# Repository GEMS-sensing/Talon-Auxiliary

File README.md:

<!--  -->

# Talon-Auxiliary
Talon daughterboard for [Flight data logger](https://github.com/GEMS-sensing/DFM_-_Flight?tab=readme-ov-file). Designed to interface with [Kestrel](https://github.com/GEMS-sensing/Project-Kestrel) main board. This board is designed to provide data logger with support to interface with analog and pulsed digital signals.
# Repo Roadmap
#### [Documents](Documents/) 

General document and image storage for repo and README

#### [Hardware](Hardware/)

Current board files (Eagle), Bill of Materials (BoM), and other design documents

#### [Production](Production/)

Contains the various Gerber and pick and place files required to have the Printed Circuit Boards (PCBs) manufactured or populated 

#### [Software](Software/)

The software associated with the piece of hardware, this is usually diagnostic software used for verifying or investigating the hardware

<!-- #### [Mechanical](Mechanical/)

Mechanical design files and assembly documents -->

<!-- #### [Testing](Testing/)

Scripts and results from the testing process and development process. Contains more detailed information about documented issues among other testing. 
 -->

## Overview
* **Type:** Talon
* **Interfaces:** Analog, digital, digital (open drain)
* **Release Version:** v1.5 - 2023/05/15

<!--  -->

## Features
### On-Board
* High precision ADC interface
	* 5V input
	* PGA
	* 16 bit (93.75 &mu;V @ 5V input, 3.9 &mu;V @ 0.25V input)
	* up to 860 SPS (reduced resolution)
* Hardware pulse counter
	* Reduces power consumption of logger by eliminating need to wake up SoM for frequent pulse interrupts 
	* 16 bit (65536) pulse count limit
	* Analog front end with hysteresis to deal with noisy inputs
	* Support for self diagnostics to allow for automated testing of operation 
* Push-pull and Open-drain compatible inputs 
* Load switch control for each port with current limiting 
* Manual switches to select each port between 3v3 and 5v power/logic
	* Chosen to be manual to prevent a firmware bug from damaging a sensor
* EEPROM with UUID built in - can store additional values defined by firmware to track offsets, etc
* ESD protected inputs

### Interface - Sensor
* I<sup>2</sup>C data interface
* M12 circular connector 

<!-- <picture>
  <source media="(prefers-color-scheme: dark)" srcset="Documents/Images/Pinout_LIGHT.png">
  
</picture> -->

| **Pin** | **Connection** | **Description** |
|---------|----------------| --------------- |
| 1     | Power (3.3V  **OR** 5V) | Output power to sensors, limited to 50mA continuous current, voltage level is selected by DIP switch next to each port |
| 2     | Open Drain            | Input for switch based sensors - 10k&Omega; pullup to Power rail|
| 3     | Ground            | Power and data ground for system |
| 4      | Analog            | Analog voltage input |
| 5      | Digital | Digital pulse input |

#### Sensor Wiring

- Switch based sensors
	- e.g. reed switch, hall effect, etc
	- Devices where the sensor open or closes a switch depending on state
	- Wire switch between Ground and Open Drain lines
	- WARNING: The Talon will apply rail power to the switch line via a pullup resistor - ensure the sensor is rated for the rail voltage being used (3.3V or 5V)
	- NOTE: To limit power consumption, only recommended for Nominally Open (NO) switches
- Pulse based sensors
	- e.g. microcontroller pulse outputs, basic digital sensors, etc
	- Devices where the output is either 0V or a logic voltage based based on a sensor state
	- Wire grounds together and wire the pulse output to the Digital pin, wire Power to sensor if needed
	- NOTE: The digital input is 5V tolerant regardless of the voltage on the power bus
- Analog based sensors
	- e.g. Potentiometers, basic sensors with variable voltage output, etc
	- Devices where the output is a voltage which varies with sensed value
	- Wire grounds together and wire the analog output of the sensor to the Analog pin, wire Power to sensor if needed
	- NOTE: The analog input is rated up to 5V regardless of the voltage on the power bus

#### Bus Selection
The power provided by each Aux Talon port can be selected as either 3.3V (default) or 5V - depending on the demands of the sensor.

This setting is changed by flipping the DIP switches (`S1`, `S2`, `S3`) on the Aux Talon itself, the position for a given voltage is noted next to each switch. Each switch controls the Aux Talon port it is adjacent to and each port can be switched independently of the others.

> [!WARNING]
> Application of voltage beyond the sensor specifications may result in irreparable damage to the sensor!

<!-- ### Interface
* I<sup>2</sup>C
* M12 circular connector  -->

<!-- <picture>
  <source media="(prefers-color-scheme: dark)" srcset="Documents/Pinout_LIGHT.png">
  
</picture> -->

<!-- ## Specifications
* **Voltage - Supply:** 3.3V
* **Voltage - Logic:** 3.3V
* **Input Current (Avg, 1s period): 30.95&mu;A @ 3.3V**
* **Input Current (Avg, 5s period): 107.43&mu;A @ 3.3V**
* **Input Current (Max): 0.45mA @ 3.3V**

#### Sensor
**Temperature** [^1]
* Range: -40 ~ 125°C 
* Accuracy: &plusmn; 0.2°C
* Repeatability: &plusmn; 0.04°C

**Pressure** [^2]
* Range: 300 ~ 1200 hPa  
* Accuracy: &plusmn; 1 hPa
* Repeatability: &plusmn; 0.06 hPa

**Humidity** [^1]
* Range: 0 ~ 100%
* Accuracy: &plusmn; 2%
* Repeatability: 0.08%

[^1]: [SHT31 Datasheet](https://sensirion.com/media/documents/213E6A3B/63A5A569/Datasheet_SHT3x_DIS.pdf)
[^2]: [DPS368 Datasheet](https://www.infineon.com/dgdl/Infineon-DPS368-DS-v01_00-EN.pdf?fileId=5546d46269e1c019016a0c45105d4b40) -->

<!-- ## Version History

`v0.0` - Initial primal version with screw terminal

`v0.1` - Initial 'hard mount' version, using M12 connector

`v1.0` - Removed pullup select[^3], added logic level buffer and voltage reg on input

`v1.1` - Moved via away from connector pads to prevent bridging when soldering 

`v2.0` - Fixed issue with address select jumper[^3] -->

<!-- ## Jumper Settings 

> [!IMPORTANT]
> Jumper settings valid for version `v2.0` and beyond[^3]

[^3]: See Errata

**Configuration Jumpers**
| Jumper | Purpose | Open | Closed | Default | 
| ------ | ------- | ---------- | ---------- | ----- | 
| `JP1` | I<sup>2</sup>C Address Select | Base Address<sup>&dagger;</sup> | Alt Address<sup>&Dagger;</sup> | Open |

&dagger; SHT31 = `0x44`, DPS368 = `0x76`

&Dagger; SHT31 = `0x44`, DPS368 = `0x77`
 -->

## Known Issues/Errata

None
<!-- #### Solder Jumper Stencil

**Version Affected:** All

**Issue:** Solar input does not support very low impedance sources (e.g. lead acid battery) - see details in issue [#20](https://github.com/GEMS-sensing/Project-Kestrel/issues/20)

**Workaround:** 

* Avoid use of low impedance batteries for input
* Include series impedance to prevent current spikes (not desirable)
* Perform board patch described in issue [#20](https://github.com/GEMS-sensing/Project-Kestrel/issues/20) -->

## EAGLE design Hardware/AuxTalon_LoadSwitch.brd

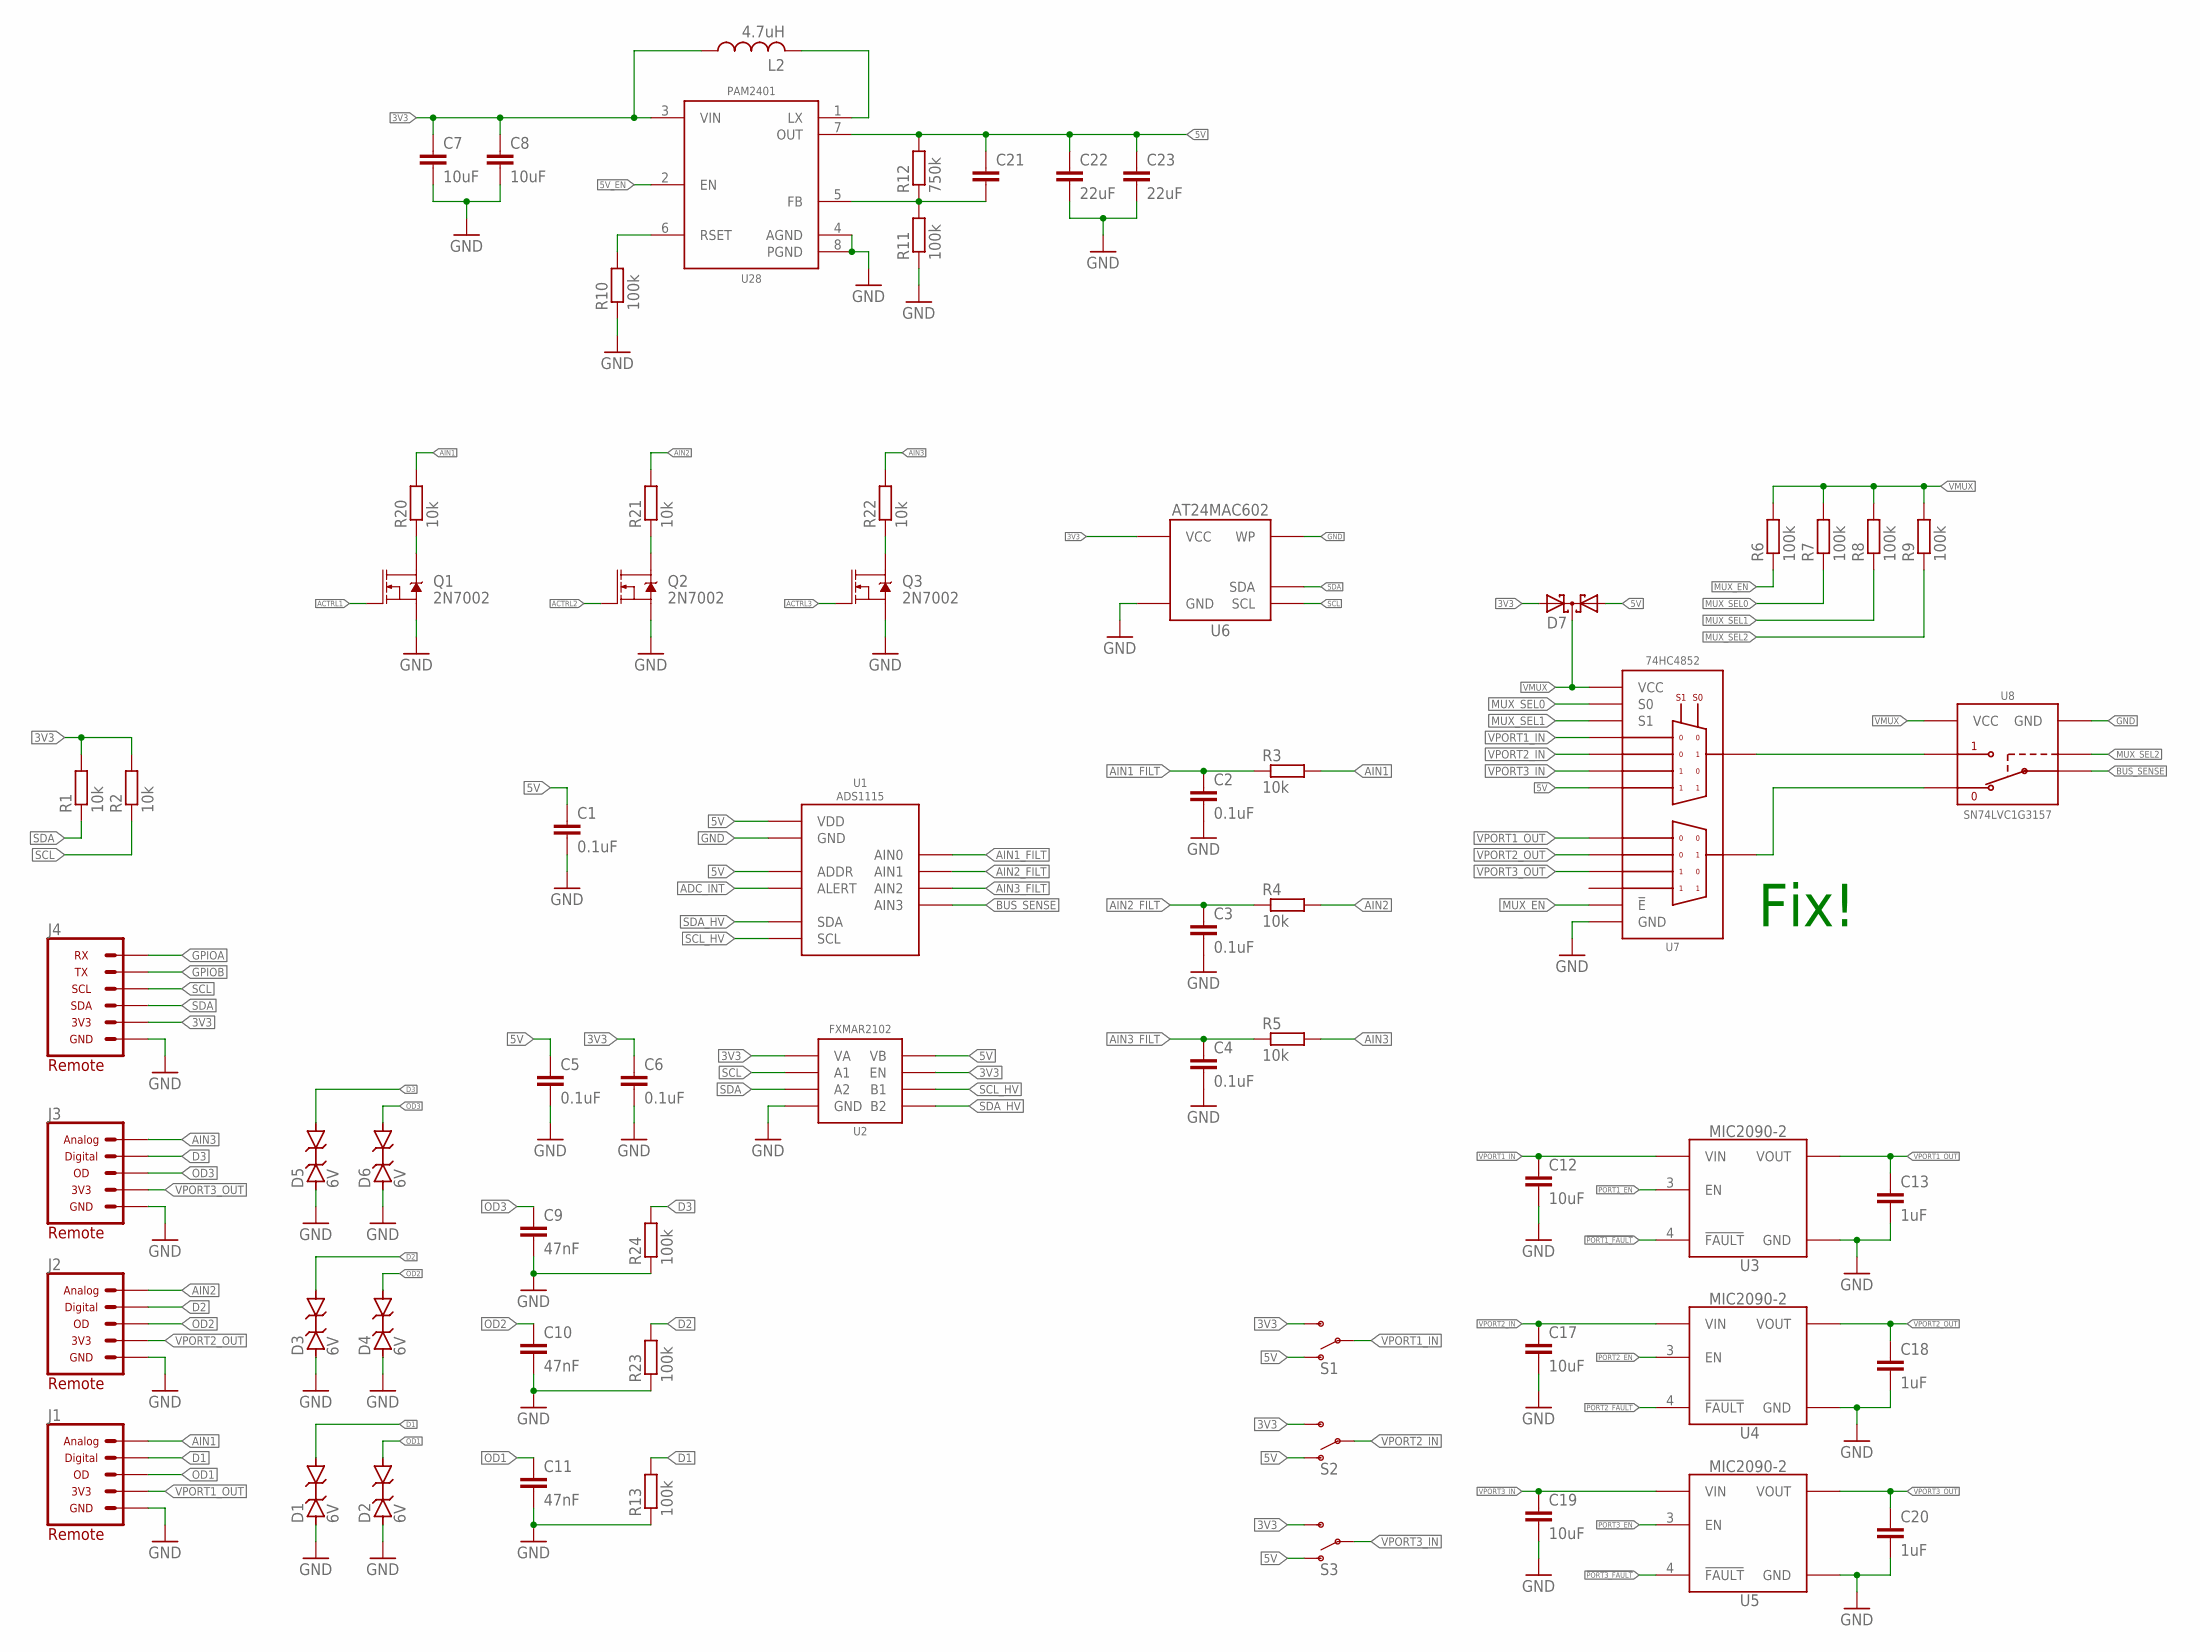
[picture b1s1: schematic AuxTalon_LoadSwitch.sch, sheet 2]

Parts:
C1, C5, C6: 0.1uF; C0402
C2, C3, C4: 0.1uF; C0805
C7, C8, C12, C17, C19: 10uF; C0805
C9, C10, C11: 47nF; C0402
C13, C18, C20: 1uF; C0603
C21: C-EUC0402; C0402; MPN DNP; DIGIKEY DNP
C22, C23: 22uF; C0805
D1, D2, D3, D4, D5, D6: 6V; D0402
D7: DIODE_CCBAT54CSOT23; SOT23-3
J1, J2, J3: CONN_AUX_M12_REMOTE; 1X05_M12_TE_T41410
J4: CONN_TALON_REMOTE; 1X06_MICROLOCKPLUS
L2: 4.7uH; WE-MAPI(2.5X2); MPN 74438323047; DIGIKEY 732-4848-1-ND
Q1, Q2, Q3: 2N7002; SOT23-3
R1, R2, R3, R4, R5, R20, R21, R22: 10k; R0402
R6, R7, R8, R9, R13, R23, R24: 100k; R0402
R10, R11: 100k; R0603
R12: 750k; R0603
S1, S2, S3: SPDTCAS-120A1; CAS-120A1
U1: ADS1115; VSSOP_10
U2: FXMAR2102UMLP; UQFN-8_1.4X1.2
U3, U4, U5: MIC2090-2; SOT23-5
U6: AT24MAC602SOT23; SOT23-5
U7: 74HC4852; VQFN-16
U8: SN74LVC1G3157SC70; DCK_R-PDSO-G6
U28: PAM2401MSOP; MSOP_8

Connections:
3V3: C6.1, C7.1, C8.1, D7.2 (A2), J4.2 (3V3), L2.P$1 (1), R1.2, R2.2, S1.3 (S), S2.3 (S), S3.3 (S), U2.1 (VA), U2.5 (EN), U6.4 (VCC), U28.3 (VIN); also elsewhere on the board
5V: C1.1, C5.1, C21.1, C22.1, C23.1, D7.1 (A1), R12.2, S1.1 (O), S2.1 (O), S3.1 (O), U1.1 (ADDR), U1.8 (VDD), U2.8 (VB), U7.11 (1Y3), U28.7 (OUT)
5V_EN: U28.2 (EN); also elsewhere on the board
!PORT1_FAULT: U3.4 (!FAULT); also elsewhere on the board
!PORT2_FAULT: U4.4 (!FAULT); also elsewhere on the board
!PORT3_FAULT: U5.4 (!FAULT); also elsewhere on the board
ACTRL1: Q1.1 (G); also elsewhere on the board
ACTRL2: Q2.1 (G); also elsewhere on the board
ACTRL3: Q3.1 (G); also elsewhere on the board
ADC_INT: U1.2 (ALERT); also elsewhere on the board
AIN1: J1.4 (ANALOG), R3.2, R20.2
AIN1_FILT: C2.1, R3.1, U1.4 (AIN0)
AIN2: J2.4 (ANALOG), R4.2, R21.2
AIN2_FILT: C3.1, R4.1, U1.5 (AIN1)
AIN3: J3.4 (ANALOG), R5.2, R22.2
AIN3_FILT: C4.1, R5.1, U1.6 (AIN2)
BUS_SENSE: U1.7 (AIN3), U8.4 (A)
D1: D1.2 (C), J1.5 (DIGITAL), R13.2; also elsewhere on the board
D2: D3.2 (C), J2.5 (DIGITAL), R23.2; also elsewhere on the board
D3: D5.2 (C), J3.5 (DIGITAL), R24.2; also elsewhere on the board
GND: C1.2, C2.2, C3.2, C4.2, C5.2, C6.2, C7.2, C8.2, C9.2, C10.2, C11.2, C12.2, C13.2, C17.2, C18.2, C19.2, C20.2, C22.2, C23.2, D1.1 (A), D2.1 (A), D3.1 (A), D4.1 (A), D5.1 (A), D6.1 (A), J1.3 (GND), J2.3 (GND), J3.3 (GND), J4.1 (GND), Q1.2 (S), Q2.2 (S), Q3.2 (S), R10.1, R11.1, R13.1, R23.1, R24.1, U1.3 (GND), U2.4 (GND), U3.2 (GND), U4.2 (GND), U5.2 (GND), U6.2 (GND), U6.5 (WP), U7.8 (GND), U7.EP (GND), U8.2 (GND), U28.4 (AGND), U28.8 (PGND); also elsewhere on the board
GPIOA: J4.6 (RX); also elsewhere on the board
GPIOB: J4.5 (TX); also elsewhere on the board
MUX_EN: R6.1, U7.6 (!E); also elsewhere on the board
MUX_SEL0: R7.1, U7.10 (S0); also elsewhere on the board
MUX_SEL1: R8.1, U7.9 (S1); also elsewhere on the board
MUX_SEL2: R9.1, U8.6 (S); also elsewhere on the board
unnamed: U7.3 (2Z), U8.3 (B1)
unnamed: R10.2, U28.6 (RSET)
unnamed: C21.2, R11.2, R12.1, U28.5 (FB)
unnamed: Q3.3 (D), R22.1
unnamed: Q2.3 (D), R21.1
unnamed: Q1.3 (D), R20.1
unnamed: L2.P$2 (2), U28.1 (LX)
unnamed: U7.13 (1Z), U8.1 (B2)
OD1: C11.1, D2.2 (C), J1.2 (DIGITAL_OPENDRAIN); also elsewhere on the board
OD2: C10.1, D4.2 (C), J2.2 (DIGITAL_OPENDRAIN); also elsewhere on the board
OD3: C9.1, D6.2 (C), J3.2 (DIGITAL_OPENDRAIN); also elsewhere on the board
PORT1_EN: U3.3 (EN); also elsewhere on the board
PORT2_EN: U4.3 (EN); also elsewhere on the board
PORT3_EN: U5.3 (EN); also elsewhere on the board
SCL: J4.4 (SCL), R2.1, U2.2 (A1), U6.1 (SCL); also elsewhere on the board
SCL_HV: U1.10 (SCL), U2.7 (B1)
SDA: J4.3 (SDA), R1.1, U2.3 (A2), U6.3 (SDA); also elsewhere on the board
SDA_HV: U1.9 (SDA), U2.6 (B2)
VMUX: D7.3 (C), R6.2, R7.2, R8.2, R9.2, U7.16 (VCC), U8.5 (VCC)
VPORT1_IN: C12.1, S1.2, U3.1 (VIN), U7.12 (1Y0)
VPORT1_OUT: C13.1, J1.1 (3V3), U3.5 (VOUT), U7.1 (2Y0)
VPORT2_IN: C17.1, S2.2, U4.1 (VIN), U7.14 (1Y1)
VPORT2_OUT: C18.1, J2.1 (3V3), U4.5 (VOUT), U7.5 (2Y1)
VPORT3_IN: C19.1, S3.2, U5.1 (VIN), U7.15 (1Y2)
VPORT3_OUT: C20.1, J3.1 (3V3), U5.5 (VOUT), U7.2 (2Y2)

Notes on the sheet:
Fix!

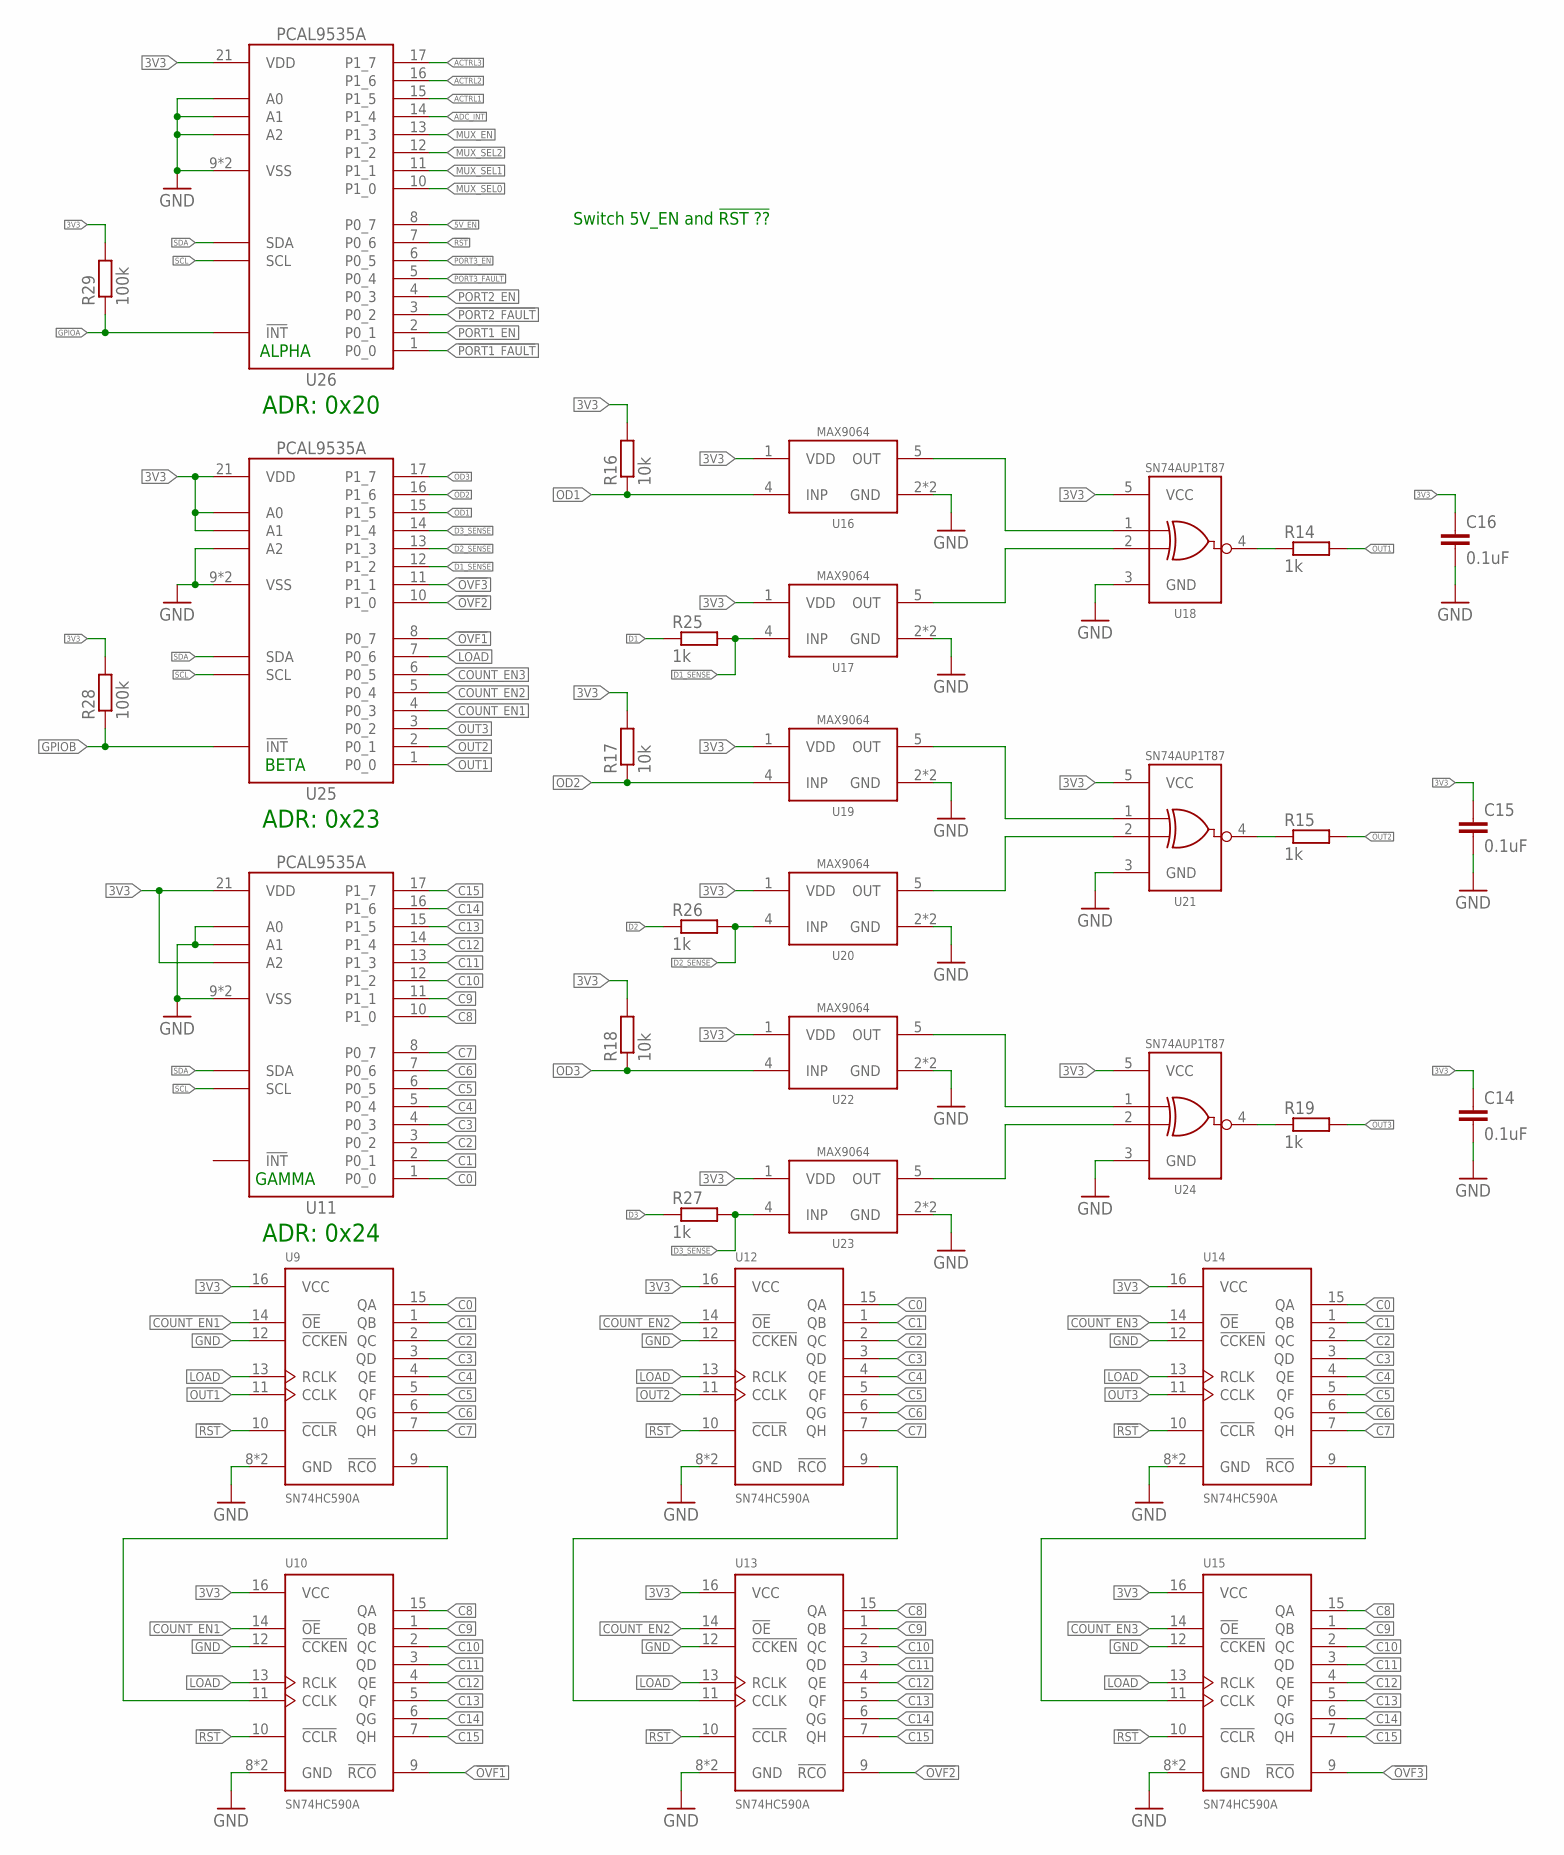
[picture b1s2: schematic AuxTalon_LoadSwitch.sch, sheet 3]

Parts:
C14, C15, C16: 0.1uF; C0402
R14, R15, R19, R25, R26, R27: 1k; R0402
R16, R17, R18: 10k; R0402
R28, R29: 100k; R0402
U9, U10, U12, U13, U14, U15: SN74HC590AVQFN; VQFN-16
U11, U25, U26: PCAL9535AQFN; QFN24
U16, U17, U19, U20, U22, U23: MAX9064; SOT23-5
U18, U21, U24: SN74AUP1T87; DCK_R-PDSO-G5

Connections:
3V3: C14.1, C15.1, C16.1, R16.2, R17.2, R18.2, R28.2, R29.2, U9.16 (VCC), U10.16 (VCC), U11.21 (VDD), U11.24 (A2), U12.16 (VCC), U13.16 (VCC), U14.16 (VCC), U15.16 (VCC), U16.1 (VDD), U17.1 (VDD), U18.5 (VCC), U19.1 (VDD), U20.1 (VDD), U21.5 (VCC), U22.1 (VDD), U23.1 (VDD), U24.5 (VCC), U25.18 (A0), U25.21 (VDD), U25.23 (A1), U26.21 (VDD); also elsewhere on the board
5V_EN: U26.8 (P0_7); also elsewhere on the board
!OVF1: U10.9 (!RCO), U25.8 (P0_7)
!OVF2: U13.9 (!RCO), U25.10 (P1_0)
!OVF3: U15.9 (!RCO), U25.11 (P1_1)
!PORT1_FAULT: U26.1 (P0_0); also elsewhere on the board
!PORT2_FAULT: U26.3 (P0_2); also elsewhere on the board
!PORT3_FAULT: U26.5 (P0_4); also elsewhere on the board
!RST: U9.10 (!CCLR), U10.10 (!CCLR), U12.10 (!CCLR), U13.10 (!CCLR), U14.10 (!CCLR), U15.10 (!CCLR), U26.7 (P0_6)
ACTRL1: U26.15 (P1_5); also elsewhere on the board
ACTRL2: U26.16 (P1_6); also elsewhere on the board
ACTRL3: U26.17 (P1_7); also elsewhere on the board
ADC_INT: U26.14 (P1_4); also elsewhere on the board
C0: U9.15 (QA), U11.1 (P0_0), U12.15 (QA), U14.15 (QA)
C1: U9.1 (QB), U11.2 (P0_1), U12.1 (QB), U14.1 (QB)
C2: U9.2 (QC), U11.3 (P0_2), U12.2 (QC), U14.2 (QC)
C3: U9.3 (QD), U11.4 (P0_3), U12.3 (QD), U14.3 (QD)
C4: U9.4 (QE), U11.5 (P0_4), U12.4 (QE), U14.4 (QE)
C5: U9.5 (QF), U11.6 (P0_5), U12.5 (QF), U14.5 (QF)
C6: U9.6 (QG), U11.7 (P0_6), U12.6 (QG), U14.6 (QG)
C7: U9.7 (QH), U11.8 (P0_7), U12.7 (QH), U14.7 (QH)
C8: U10.15 (QA), U11.10 (P1_0), U13.15 (QA), U15.15 (QA)
C9: U10.1 (QB), U11.11 (P1_1), U13.1 (QB), U15.1 (QB)
C10: U10.2 (QC), U11.12 (P1_2), U13.2 (QC), U15.2 (QC)
C11: U10.3 (QD), U11.13 (P1_3), U13.3 (QD), U15.3 (QD)
C12: U10.4 (QE), U11.14 (P1_4), U13.4 (QE), U15.4 (QE)
C13: U10.5 (QF), U11.15 (P1_5), U13.5 (QF), U15.5 (QF)
C14: U10.6 (QG), U11.16 (P1_6), U13.6 (QG), U15.6 (QG)
C15: U10.7 (QH), U11.17 (P1_7), U13.7 (QH), U15.7 (QH)
COUNT_EN1: U9.14 (!OE), U10.14 (!OE), U25.4 (P0_3)
COUNT_EN2: U12.14 (!OE), U13.14 (!OE), U25.5 (P0_4)
COUNT_EN3: U14.14 (!OE), U15.14 (!OE), U25.6 (P0_5)
D1: R25.1; also elsewhere on the board
D1_SENSE: R25.2, U17.4 (INP), U25.12 (P1_2)
D2: R26.1; also elsewhere on the board
D2_SENSE: R26.2, U20.4 (INP), U25.13 (P1_3)
D3: R27.1; also elsewhere on the board
D3_SENSE: R27.2, U23.4 (INP), U25.14 (P1_4)
GND: C14.2, C15.2, C16.2, U9.8 (GND), U9.12 (!CCKEN), U9.EP (GND), U10.8 (GND), U10.12 (!CCKEN), U10.EP (GND), U11.9 (VSS), U11.18 (A0), U11.23 (A1), U11.EP (VSS), U12.8 (GND), U12.12 (!CCKEN), U12.EP (GND), U13.8 (GND), U13.12 (!CCKEN), U13.EP (GND), U14.8 (GND), U14.12 (!CCKEN), U14.EP (GND), U15.8 (GND), U15.12 (!CCKEN), U15.EP (GND), U16.2 (GND), U16.3 (GND), U17.2 (GND), U17.3 (GND), U18.3 (GND), U19.2 (GND), U19.3 (GND), U20.2 (GND), U20.3 (GND), U21.3 (GND), U22.2 (GND), U22.3 (GND), U23.2 (GND), U23.3 (GND), U24.3 (GND), U25.9 (VSS), U25.24 (A2), U25.EP (VSS), U26.9 (VSS), U26.18 (A0), U26.23 (A1), U26.24 (A2), U26.EP (VSS); also elsewhere on the board
GPIOA: R29.1, U26.22 (!INT); also elsewhere on the board
GPIOB: R28.1, U25.22 (!INT); also elsewhere on the board
LOAD: U9.13 (RCLK), U10.13 (RCLK), U12.13 (RCLK), U13.13 (RCLK), U14.13 (RCLK), U15.13 (RCLK), U25.7 (P0_6)
MUX_EN: U26.13 (P1_3); also elsewhere on the board
MUX_SEL0: U26.10 (P1_0); also elsewhere on the board
MUX_SEL1: U26.11 (P1_1); also elsewhere on the board
MUX_SEL2: U26.12 (P1_2); also elsewhere on the board
unnamed: U9.9 (!RCO), U10.11 (CCLK)
unnamed: U12.9 (!RCO), U13.11 (CCLK)
unnamed: U14.9 (!RCO), U15.11 (CCLK)
unnamed: U20.5 (OUT), U21.2 (B)
unnamed: U19.5 (OUT), U21.1 (A)
unnamed: U16.5 (OUT), U18.1 (A)
unnamed: U17.5 (OUT), U18.2 (B)
unnamed: U23.5 (OUT), U24.2 (B)
unnamed: U22.5 (OUT), U24.1 (A)
unnamed: R14.1, U18.4 (Y)
unnamed: R15.1, U21.4 (Y)
unnamed: R19.1, U24.4 (Y)
OD1: R16.1, U16.4 (INP), U25.15 (P1_5); also elsewhere on the board
OD2: R17.1, U19.4 (INP), U25.16 (P1_6); also elsewhere on the board
OD3: R18.1, U22.4 (INP), U25.17 (P1_7); also elsewhere on the board
OUT1: R14.2, U9.11 (CCLK), U25.1 (P0_0)
OUT2: R15.2, U12.11 (CCLK), U25.2 (P0_1)
OUT3: R19.2, U14.11 (CCLK), U25.3 (P0_2)
PORT1_EN: U26.2 (P0_1); also elsewhere on the board
PORT2_EN: U26.4 (P0_3); also elsewhere on the board
PORT3_EN: U26.6 (P0_5); also elsewhere on the board
SCL: U11.19 (SCL), U25.19 (SCL), U26.19 (SCL); also elsewhere on the board
SDA: U11.20 (SDA), U25.20 (SDA), U26.20 (SDA); also elsewhere on the board

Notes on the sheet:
BETA
GAMMA
ALPHA
ADR: 0x20
ADR: 0x23
ADR: 0x24
Switch 5V_EN and !RST ??

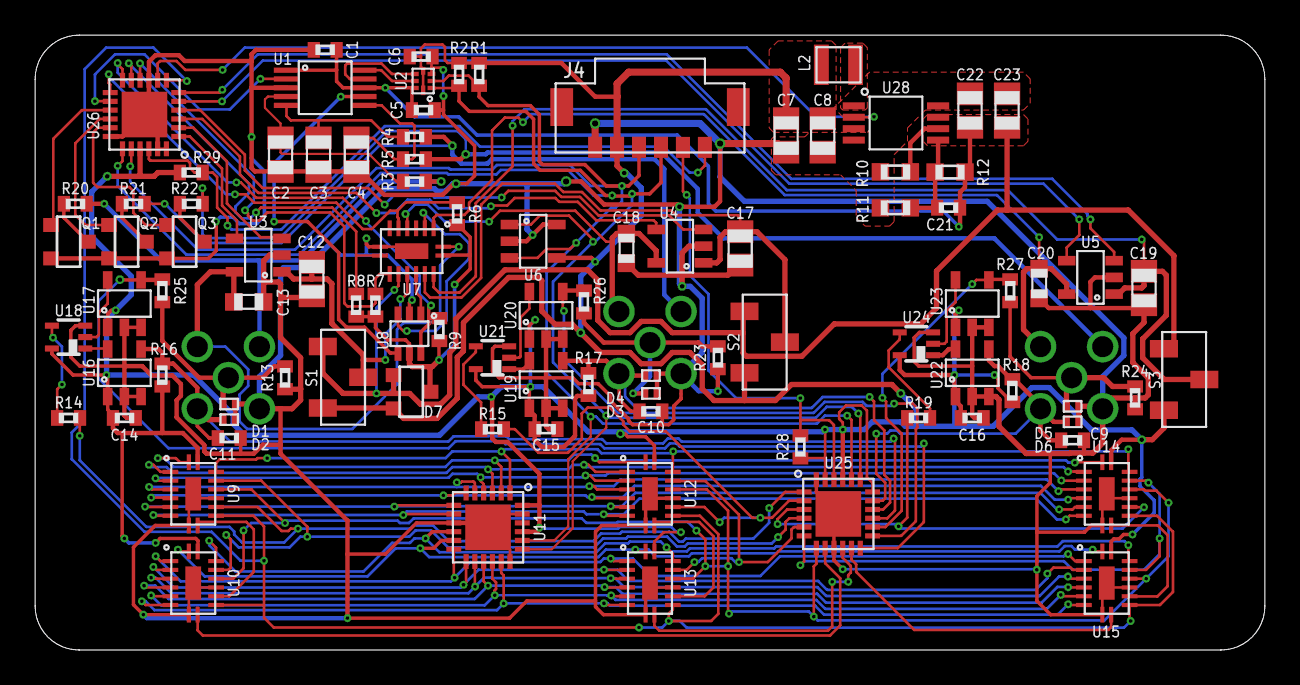
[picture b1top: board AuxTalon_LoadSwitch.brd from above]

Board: 2 copper layers, 70.0 x 35.0 mm, 97 parts (0 on the bottom side), 94 nets.

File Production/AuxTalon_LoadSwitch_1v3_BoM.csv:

"Qty","Value","Device","Package","Parts","Description","DIGIKEY","DISP","MF","MOUSER","MPN","VALUE","VALUE_PART",
"1","","C-EUC0402","C0402","C21","CAPACITOR, European symbol","DNP","","N/A","","DNP","","",
"1","","DIODE_CCBAT54CSOT23","SOT23-3","D7","Dual Diode, Common Cathode","BAT54CLT1GOSCT-ND","","ON Semiconductor","","BAT54CLT1G","","",
"6","","SN74HC590AVQFN","VQFN-16","U9, U10, U12, U13, U14, U15","SN74HC590A - 8 bit binary counter with direct clear","1727-6923-1-ND","","Nexperia","","74HC590BQ","115","",
"9","0.1uF","C-EU0.1UFC0402","C0402","C1, C5, C6, C13, C14, C15, C16, C18, C20","CAPACITOR, European symbol","490-4759-1-ND","","Murata","","GCM155R71C104KA55D","","",
"3","0.1uF","C-EU0.1UFC0805","C0805","C2, C3, C4","CAPACITOR, European symbol","399-8000-1-ND","","Kemet","","C0805C104M3RACTU","","",
"8","100k","R-EU_100KR0402","R0402","R6, R7, R8, R9, R10, R13, R23, R24","RESISTOR, European symbol","311-100KLRCT-ND","","Yageo","","RC0402FR-07100KL","","100k",
"1","100k","R-EU_100KR0603","R0603","R11","RESISTOR, European symbol","311-100KHRCT-ND","","Yageo","","RC0603FR-07100KL","","100k",
"8","10k","R-EU_10KR0402","R0402","R1, R2, R3, R4, R5, R16, R17, R18","RESISTOR, European symbol","311-10.0KLRCT-ND","","Yageo","","RC0402FR-0710KL","","10k",
"1","10k","R-EU_10KR0603","R0603","R21","RESISTOR, European symbol","311-10.0KHRCT-ND","","Yageo","","RC0603FR-0710KL","","10k",
"5","10uF","C-EU10UFC0805","C0805","C7, C8, C12, C17, C19","CAPACITOR, European symbol","490-6473-1-ND","","Murata","","GRM21BR61C106KE15K","","",
"1","150k","R-EU_150KR0603","R0603","R22","RESISTOR, European symbol","311-150KHRCT-ND","","Yageo","","RC0603FR-07150KL","","150k",
"2","22uF","C-EU22UFC0805","C0805","C22, C23","CAPACITOR, European symbol","490-9952-1-ND","","Murata","","GRM219R61C226ME15L","","",
"1","24AA02SOT23","24AA02SOT23","SOT23-5","U6","24AA02 - 2k I2C Serial EEPROM","24AA025E64T-I/OTCT-ND","24AA025E64","Microchip","24AA025E64T-I/OTCT-ND","24AA025E64T-I/OT","","",
"1","4.7uH","INDUCTOR_MAPI_2.5X2","WE-MAPI(2.5X2)","L2","Genaric Inductor","732-4848-1-ND","","Wurth","","74438323047","","",
"3","47nF","C-EU47NFC0402","C0402","C9, C10, C11","CAPACITOR, European symbol","490-3254-1-ND","","Murata","","GRM155R71E473KA88D","","",
"2","62k","R-EU_62KR0603","R0603","R15, R19","RESISTOR, European symbol","RMCF0603FT62K0CT-ND","","Stackpole","","RMCF0603FT62K0","","62k",
"6","6V","DIODE_ESD_BI_D5V0L1_0402","D0402","D1, D2, D3, D4, D5, D6","Generic Bidirectional ESD Diode","D5V0L1B2LP4-7BDICT-ND","","Diodes Inc","","D5V0L1B2LP4-7B","6V","",
"1","74HC4852","74HC4852","VQFN-16","U7","74HC4852  - Analog Multiplexer, Dual 4-Channel (1:4 x 2)","1727-7953-1-ND","74HC4852","Nexperia","","74HC4852BQ-Q100","11","",
"1","750k","R-EU_750KR0603","R0603","R12","RESISTOR, European symbol","311-750KHRCT-ND","","Yageo","","RC0603FR-07750KL","","750k",
"2","82k","R-EU_82KR0603","R0603","R14, R20","RESISTOR, European symbol","CR0603-FX-8202ELFCT-ND","","Bourns","","CR0603-FX-8202ELF","","82k",
"1","ADS1115","ADS1115","VSSOP_10","U1","ADS1115 - Sigma Delta ADC","296-38849-1-ND","","TI","","ADS1115IDGSR","","",
"3","CONN_AUX_M12_REMOTE","CONN_AUX_M12_REMOTE","1X05_M12_TE_T41410","J1, J2, J3","GEMS Connector for Auiliary Port Devices","A126851-ND","Remote","TE","","T4141012051-000","","",
"1","CONN_TALON_REMOTE","CONN_TALON_REMOTE","1X06_MICROLOCKPLUS","J4","GEMS Connector for Talon Interface","900-2059570671CT-ND","Remote","Molex","","2059570671","","",
"1","FXMAR2102UMLP","FXMAR2102UMLP","UQFN-8_1.4X1.2","U2","FXMAR2102 - 2 Channel Bidirectional Voltage Level Translator for I2C Applications","FXMAR2102UMX-F106CT-ND","FXMAR2102","OnSemi","","FXMAR2102UMX-F106","","",
"6","MAX9064","MAX9064","SOT23-5","U16, U17, U19, U20, U22, U23","MAX906x - Ultra-Small nanoPower Single Comparator","MAX9064EUK+TCT-ND","MAX9064","Maxim","","MAX9064EUK+T","","",
"3","MCP23018QFN","MCP23018QFN","QFN24","U11, U25, U26","MCP23018 - I2C I/O Expander, 16 bit wtih interrupt and reset","MCP23018T-E/MJCT-ND","","TI","","MCP23018T-E/MJ","","",
"1","PAM2401MSOP","PAM2401MSOP","MSOP_8","U28","PAM2401 - Step-Up (Boost) DC-DC Converter","PAM2401SCADJDICT-ND","","Diodes Inc","","PAM2401SCADJ","","",
"3","SN74AUP1T87","SN74AUP1T87","DCK_R-PDSO-G5","U18, U21, U24","SN74AUP1T87 - XNOR, 1 Element, 2 Input","296-27398-1-ND","SN74AUP1T87","TI","","SN74AUP1T87DCKR","","",
"1","SN74LVC1G3157SC70","SN74LVC1G3157SC70","DCK_R-PDSO-G6","U8","SN74LVC1G3157 - SPDT Analog Switch","296-14909-1-ND","SN74LVC1G3157","TI","","SN74LVC1G3157DCKR","","",
"3","SPDTCAS-120A1","SPDTCAS-120A1","CAS-120A1","S1, S2, S3","Genaric SPDT switch","CAS120JCT-ND","","Nidec Copal","","CAS-120TA","","",
"3","TPS22944","TPS22944","DCK_R-PDSO-G5","U3, U4, U5","TPS2294x - Low Input Voltage Current Limited Load Switch with Shut off and Auto Restart","2156-FPF2006-ND","FPF2006","Fairchild","","FPF2006","","",

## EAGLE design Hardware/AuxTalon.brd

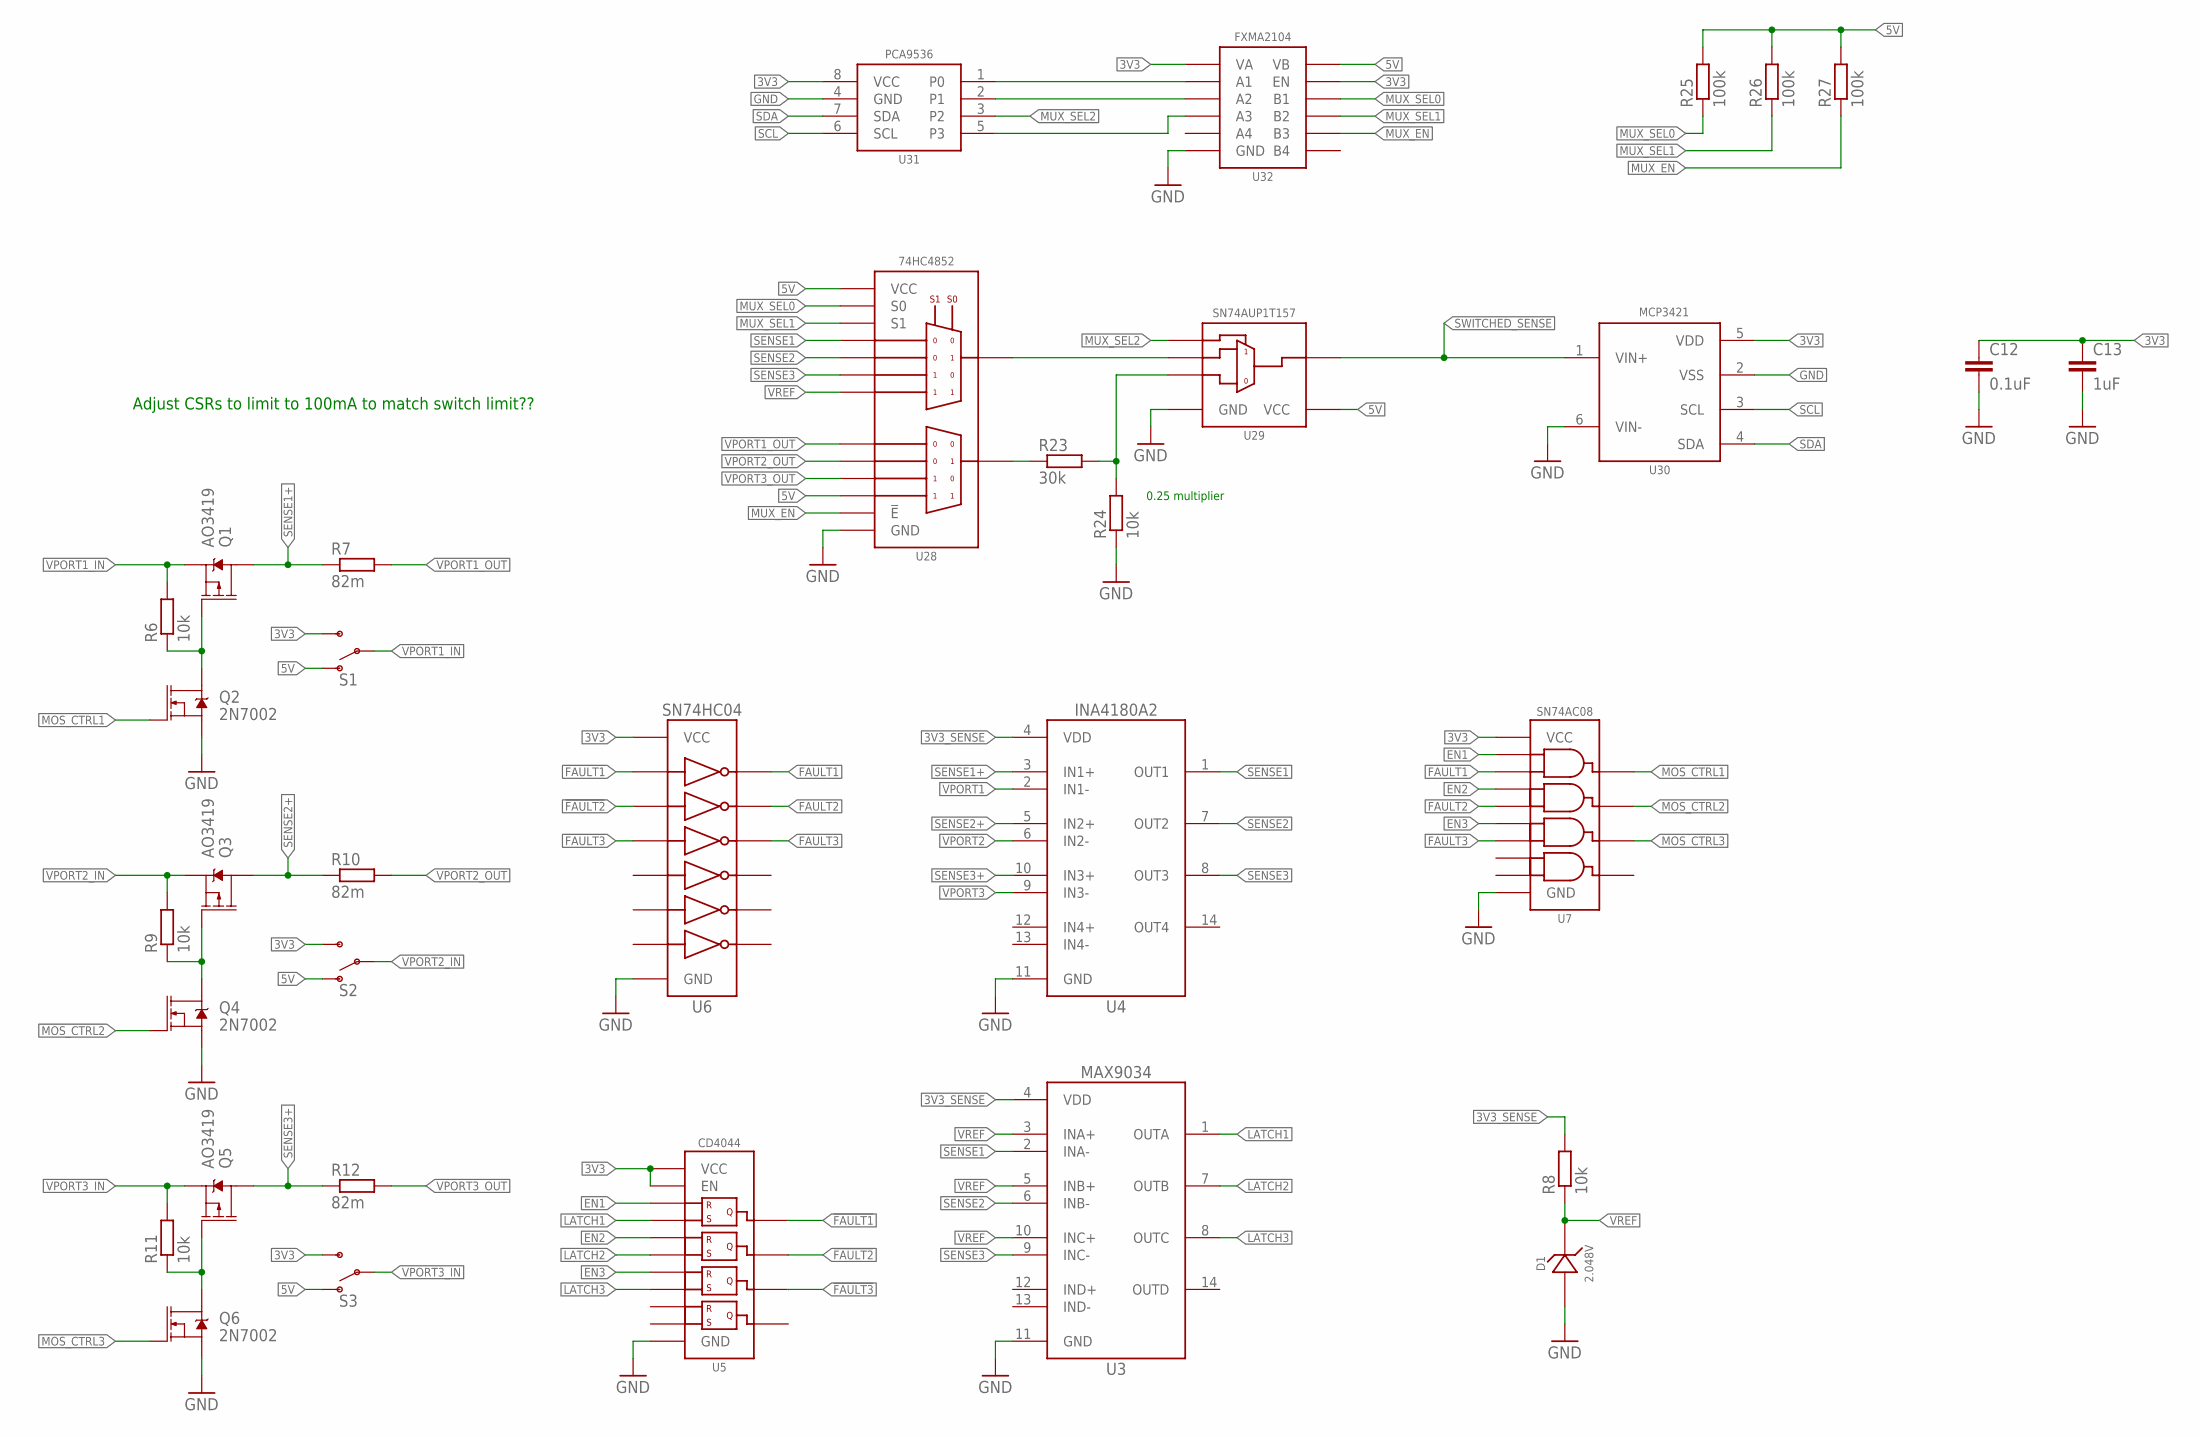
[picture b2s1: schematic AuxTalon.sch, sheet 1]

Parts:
C12: 0.1uF; C0402
C13: 1uF; C0805
D1: 2.048V; SOT23-3
Q1, Q3, Q5: AO3419; SOT23-3
Q2, Q4, Q6: 2N7002; SOT23-3
R6, R8, R9, R11, R24: 10k; R0402
R7, R10, R12: 82m; R0603
R23: 30k; R0402
R25, R26, R27: 100k; R0402
S1, S2, S3: SPDTCAS-120A1; CAS-120A1
U3: MAX9034TSSOP; TSSOP14
U4: INA4180A2; TSSOP14
U5: CD4044; TSSOP16
U6: SN74HC04; TSSOP14
U7: SN74AC08; TSSOP14
U28: 74HC4852; VQFN-16
U29: SN74AUP1T157DCK; DCK_R-PDSO-G6
U30: MCP3421A3; SOT23-6L
U31: PCA9536DFN; DFN_8_3X3
U32: FXMA2104; MLP_12

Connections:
3V3: C12.1, C13.1, S1.3 (S), S2.3 (S), S3.3 (S), U5.5 (EN), U5.16 (VCC), U6.14 (VCC), U7.14 (VCC), U30.5 (VDD), U31.8 (VCC), U32.2 (VA), U32.8 (EN); also elsewhere on the board
3V3_SENSE: R8.2, U3.4 (VDD), U4.4 (VDD); also elsewhere on the board
5V: R25.2, R26.2, R27.2, S1.1 (O), S2.1 (O), S3.1 (O), U28.4 (2Y3), U28.16 (VCC), U29.5 (VCC), U32.1 (VB); also elsewhere on the board
!FAULT1: U5.13 (Q1), U6.1 (A1); also elsewhere on the board
!FAULT2: U5.9 (Q2), U6.3 (A2); also elsewhere on the board
!FAULT3: U5.10 (Q3), U6.5 (A3); also elsewhere on the board
EN1: U5.4 (R1), U7.1 (A1); also elsewhere on the board
EN2: U5.6 (R2), U7.4 (A2); also elsewhere on the board
EN3: U5.12 (R3), U7.9 (A3); also elsewhere on the board
FAULT1: U6.2 (Y1), U7.2 (B1)
FAULT2: U6.4 (Y2), U7.5 (B2)
FAULT3: U6.6 (Y3), U7.10 (B3)
GND: C12.2, C13.2, D1.2 (A), Q2.2 (S), Q4.2 (S), Q6.2 (S), R24.1, U3.11 (GND), U4.11 (GND), U5.8 (GND), U6.7 (GND), U7.7 (GND), U28.8 (GND), U28.EP (GND), U29.2 (GND), U30.2 (VSS), U30.6 (VIN-), U31.4 (GND), U32.7 (GND); also elsewhere on the board
LATCH1: U3.1 (OUTA), U5.3 (S1)
LATCH2: U3.7 (OUTB), U5.7 (S2)
LATCH3: U3.8 (OUTC), U5.11 (S3)
MOS_CTRL1: Q2.1 (G), U7.3 (Y1)
MOS_CTRL2: Q4.1 (G), U7.6 (Y2)
MOS_CTRL3: Q6.1 (G), U7.8 (Y3)
MUX_EN: R27.1, U28.6 (!E), U32.10 (B3)
MUX_SEL0: R25.1, U28.10 (S0), U32.12 (B1)
MUX_SEL1: R26.1, U28.9 (S1), U32.11 (B2)
MUX_SEL2: U29.4 (C), U31.3 (P2); also elsewhere on the board
unnamed: Q3.1 (G), Q4.3 (D), R9.1
unnamed: Q1.1 (G), Q2.3 (D), R6.1
unnamed: Q5.1 (G), Q6.3 (D), R11.1
unnamed: R23.1, U28.3 (2Z)
unnamed: R23.2, R24.2, U29.3 (B)
unnamed: U31.1 (P0), U32.3 (A1)
unnamed: U31.2 (P1), U32.4 (A2)
unnamed: U31.5 (P3), U32.5 (A3)
unnamed: U28.13 (1Z), U29.1 (A)
SCL: U30.3 (SCL), U31.6 (SCL); also elsewhere on the board
SDA: U30.4 (SDA), U31.7 (SDA); also elsewhere on the board
SENSE1: U3.2 (INA-), U4.1 (OUT1), U28.12 (1Y0)
SENSE1+: Q1.3 (D), R7.1, U4.3 (IN1+)
SENSE2: U3.6 (INB-), U4.7 (OUT2), U28.14 (1Y1)
SENSE2+: Q3.3 (D), R10.1, U4.5 (IN2+)
SENSE3: U3.9 (INC-), U4.8 (OUT3), U28.15 (1Y2)
SENSE3+: Q5.3 (D), R12.1, U4.10 (IN3+)
SWITCHED_SENSE: U29.6 (Y), U30.1 (VIN+)
VPORT1: U4.2 (IN1-)
VPORT1_IN: Q1.2 (S), R6.2, S1.2
VPORT1_OUT: R7.2, U28.1 (2Y0); also elsewhere on the board
VPORT2: U4.6 (IN2-)
VPORT2_IN: Q3.2 (S), R9.2, S2.2
VPORT2_OUT: R10.2, U28.5 (2Y1); also elsewhere on the board
VPORT3: U4.9 (IN3-)
VPORT3_IN: Q5.2 (S), R11.2, S3.2
VPORT3_OUT: R12.2, U28.2 (2Y2); also elsewhere on the board
VREF: D1.1 (C), R8.1, U3.3 (INA+), U3.5 (INB+), U3.10 (INC+), U28.11 (1Y3); also elsewhere on the board

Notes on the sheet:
Adjust CSRs to limit to 100mA to match switch limit??
0.25 multiplier
